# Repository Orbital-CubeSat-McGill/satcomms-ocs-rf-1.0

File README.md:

# satcomms-ocs-rf-1.0
OCS-RF-1.0 Project by OCS 3 (the green board)

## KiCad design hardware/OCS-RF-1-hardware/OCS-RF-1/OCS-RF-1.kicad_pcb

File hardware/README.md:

KiCad Project for the green board

library path should be added to enviorment variables to show up, or you can just import it with symbol/footprint editor

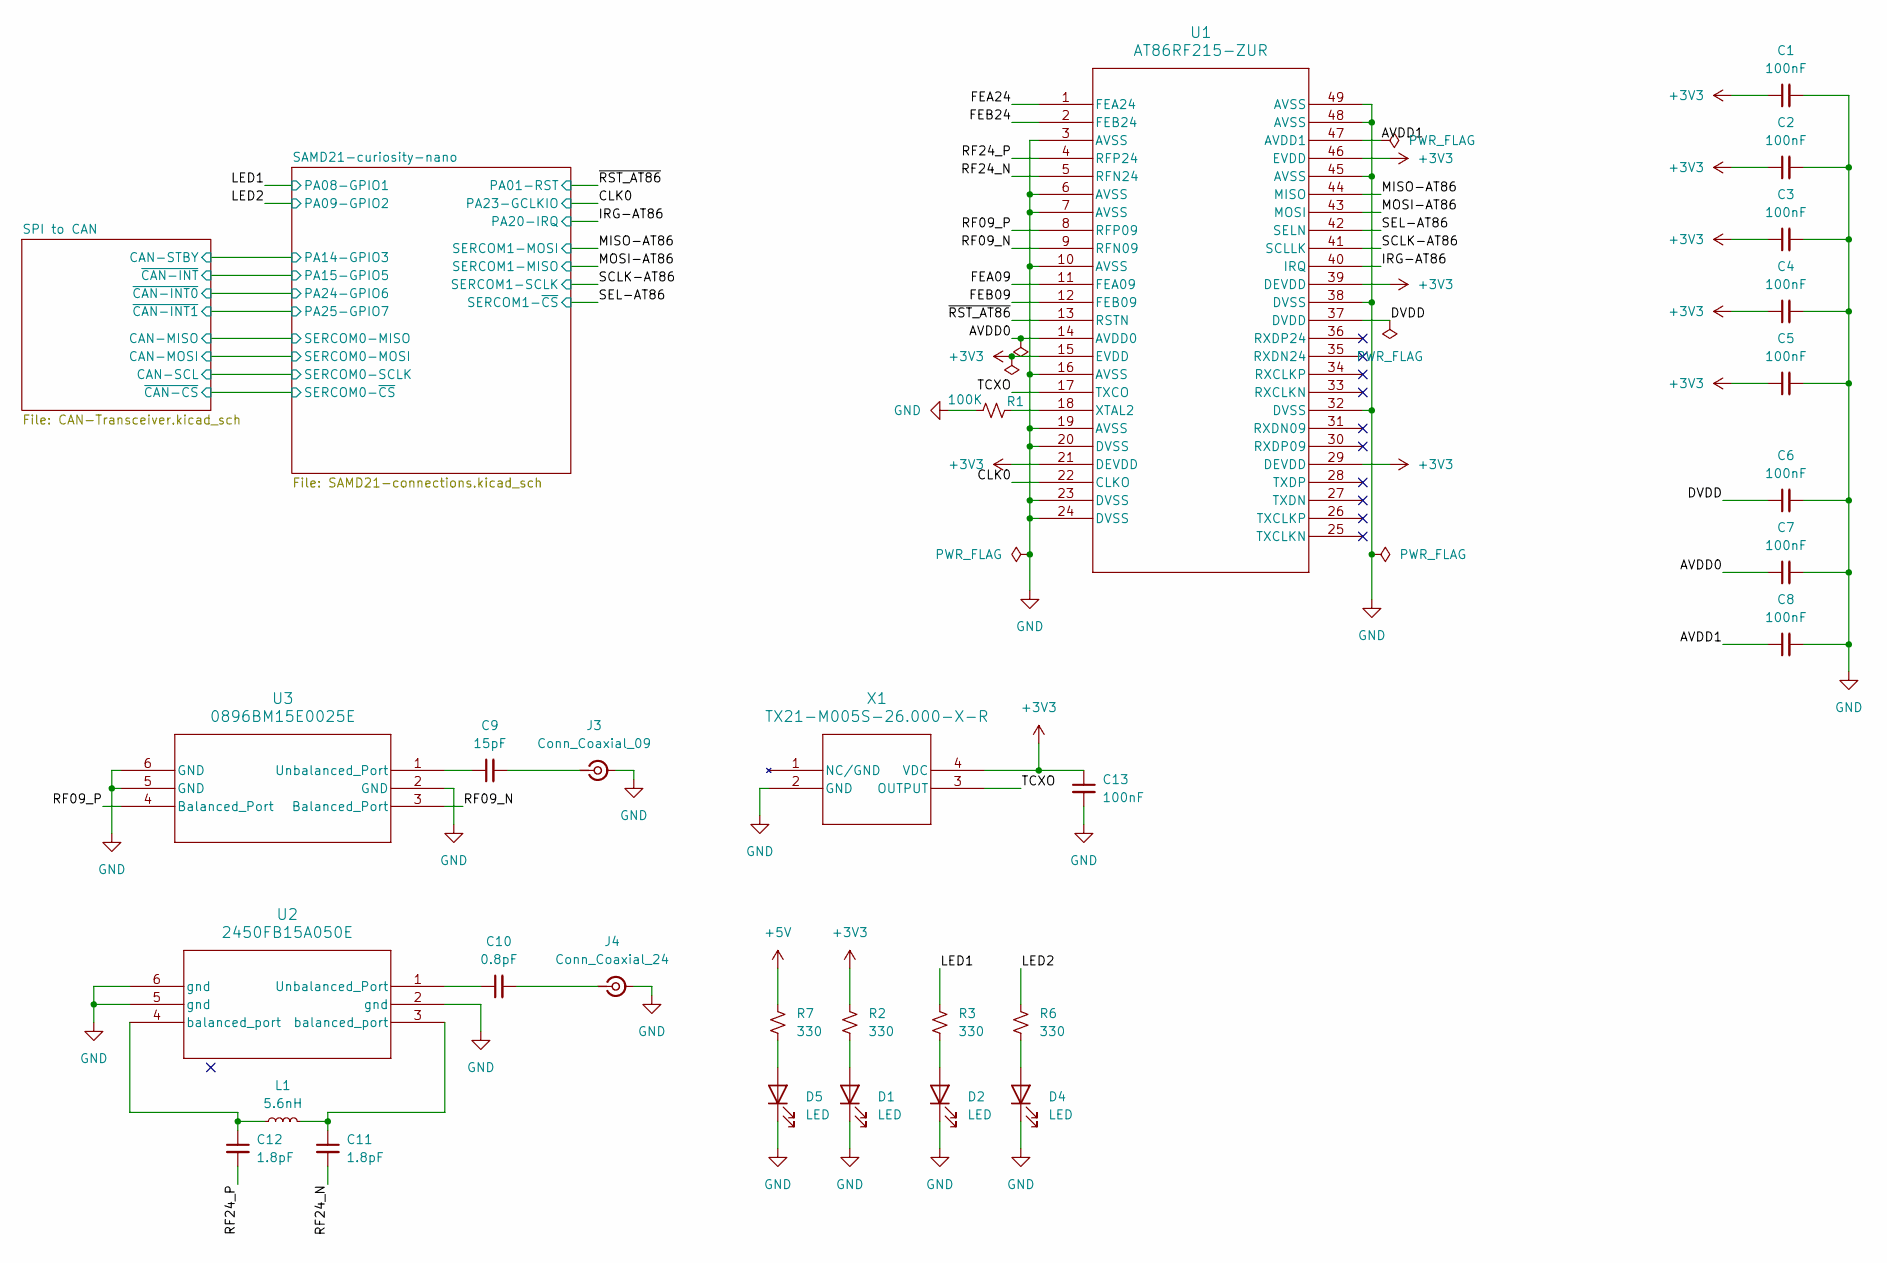
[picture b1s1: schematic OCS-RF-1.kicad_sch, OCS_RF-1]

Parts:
C1, C2, C3, C4, C5, C6, C7, C8, C13: 100nF; C_0603_1608Metric_Pad1.08x0.95mm_HandSolder
C9: 15pF; C_0402_1005Metric
C10: 0.8pF; C_0402_1005Metric
C11, C12: 1.8pF; C_0402_1005Metric
D1, D2, D4, D5: LED; LED_0603_1608Metric_Pad1.05x0.95mm_HandSolder
J3: Conn_Coaxial_09; SMA_Samtec_SMA-J-P-H-ST-EM1_EdgeMount
J4: Conn_Coaxial_24; SMA_Samtec_SMA-J-P-H-ST-EM1_EdgeMount
L1: 5.6nH; L_0402_1005Metric
R1: 100K; R_0603_1608Metric_Pad0.98x0.95mm_HandSolder
R2, R3, R6, R7: 330; R_0603_1608Metric_Pad0.98x0.95mm_HandSolder
U1: AT86RF215-ZUR; QFN48_PQ_MCH
U2: 2450FB15A050E; 2450FB15A050E_JOT
U3: 0896BM15E0025E; 0896BM15E0025E_JOT
X1: TX21-M005S-26.000-X-R; TX21_2x1p6_SMD_AKR

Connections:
+3V3: C1.1, C2.1, C3.1, C4.1, C5.1, C13.1, R2.1, U1.15 (EVDD), U1.21 (DEVDD), U1.29 (DEVDD), U1.39 (DEVDD), U1.46 (EVDD), X1.4 (VDC); also elsewhere on the board
+5V: R7.1; also elsewhere on the board
/AVDD0: C7.1, U1.14 (AVDD0)
/AVDD1: C8.1, U1.47 (AVDD1)
/CLK0: U1.22 (CLKO); also elsewhere on the board
/DVDD: C6.1, U1.37 (DVDD)
/FEA09: U1.11 (FEA09)
/FEA24: U1.1 (FEA24)
/FEB09: U1.12 (FEB09)
/FEB24: U1.2 (FEB24)
/IRG-AT86: U1.40 (IRQ); also elsewhere on the board
/LED1: R3.1; also elsewhere on the board
/LED2: R6.1; also elsewhere on the board
/MISO-AT86: U1.44 (MISO); also elsewhere on the board
/MOSI-AT86: U1.43 (MOSI); also elsewhere on the board
/RF09_N: U1.9 (RFN09), U3.3 (Balanced_Port)
/RF09_P: U1.8 (RFP09), U3.4 (Balanced_Port)
/RF24_N: C11.2, U1.5 (RFN24)
/RF24_P: C12.2, U1.4 (RFP24)
/SCLK-AT86: U1.41 (SCLLK); also elsewhere on the board
/SEL-AT86: U1.42 (SELN); also elsewhere on the board
/TCXO: U1.17 (TXCO), X1.3 (OUTPUT)
/~RST_AT86: U1.13 (RSTN); also elsewhere on the board
GND: C1.2, C2.2, C3.2, C4.2, C5.2, C6.2, C7.2, C8.2, C13.2, D1.1 (K), D2.1 (K), D4.1 (K), D5.1 (K), J3.2 (Ext), J4.2 (Ext), R1.2, U1.3 (AVSS), U1.6 (AVSS), U1.7 (AVSS), U1.10 (AVSS), U1.16 (AVSS), U1.19 (AVSS), U1.20 (DVSS), U1.23 (DVSS), U1.24 (DVSS), U1.32 (DVSS), U1.38 (DVSS), U1.45 (AVSS), U1.48 (AVSS), U1.49 (AVSS), U2.2 (gnd), U2.5 (gnd), U2.6 (gnd), U3.2 (GND), U3.5 (GND), U3.6 (GND), X1.2 (GND); also elsewhere on the board
unnamed: C11.1, L1.2, U2.3 (balanced_port)
unnamed: C12.1, L1.1, U2.4 (balanced_port)
unnamed: D1.2 (A), R2.2
unnamed: D2.2 (A), R3.2
unnamed: D4.2 (A), R6.2
unnamed: D5.2 (A), R7.2
unnamed: C9.2, J3.1 (In)
unnamed: C10.2, J4.1 (In)
unnamed: R1.1, U1.18 (XTAL2)
unnamed: C10.1, U2.1 (Unbalanced_Port)
unnamed: C9.1, U3.1 (Unbalanced_Port)

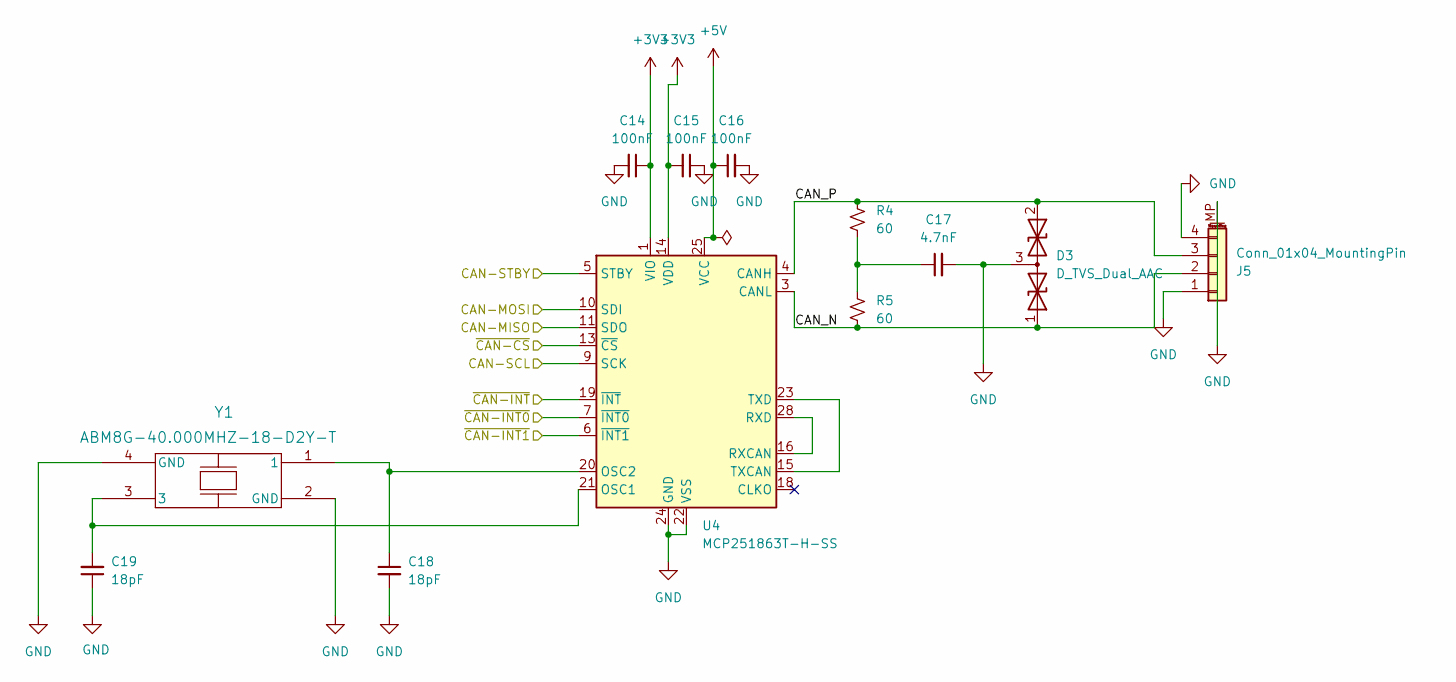
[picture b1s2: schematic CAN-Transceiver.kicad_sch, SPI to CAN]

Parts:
C14, C15, C16: 100nF; C_0603_1608Metric_Pad1.08x0.95mm_HandSolder
C17: 4.7nF; C_0603_1608Metric_Pad1.08x0.95mm_HandSolder
C18, C19: 18pF; C_0603_1608Metric_Pad1.08x0.95mm_HandSolder
D3: D_TVS_Dual_AAC; SOT-23
J5: Conn_01x04_MountingPin; JST_SH_SM04B-SRSS-TB_1x04-1MP_P1.00mm_Horizontal
R4, R5: 60; R_0603_1608Metric_Pad0.98x0.95mm_HandSolder
U4: MCP251863T-H-SS; SSOP-28_5.3x10.2mm_P0.65mm
Y1: ABM8G-40.000MHZ-18-D2Y-T; CRYSTAL_ABM8G_ABR

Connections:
+3V3: C14.1, C15.2, U4.1 (VIO), U4.14 (VDD); also elsewhere on the board
+5V: C16.1, U4.25 (VCC); also elsewhere on the board
/SAMD21-curiosity-nano/PA14-GPIO3: U4.5 (STBY); also elsewhere on the board
/SAMD21-curiosity-nano/PA15-GPIO5: U4.19 (~INT); also elsewhere on the board
/SAMD21-curiosity-nano/PA24-GPIO6: U4.7 (~INT0); also elsewhere on the board
/SAMD21-curiosity-nano/PA25-GPIO7: U4.6 (~INT1); also elsewhere on the board
/SAMD21-curiosity-nano/SERCOM0-MISO: U4.11 (SDO); also elsewhere on the board
/SAMD21-curiosity-nano/SERCOM0-MOSI: U4.10 (SDI); also elsewhere on the board
/SAMD21-curiosity-nano/SERCOM0-SCLK: U4.9 (SCK); also elsewhere on the board
/SAMD21-curiosity-nano/SERCOM0-~CS: U4.13 (~CS); also elsewhere on the board
/SPI to CAN/CAN_N: D3.1 (A1), J5.2, R5.2, U4.3 (CANL)
/SPI to CAN/CAN_P: D3.2 (A2), J5.3, R4.1, U4.4 (CANH)
GND: C14.2, C15.1, C16.2, C17.2, C18.2, C19.1, D3.3 (common), J5.1, J5.4, J5.MP (MountPin), U4.22 (VSS), U4.24 (GND), Y1.2 (GND), Y1.4 (GND); also elsewhere on the board
unnamed: C17.1, R4.2, R5.1
unnamed: C19.2, U4.21 (OSC1), Y1.3
unnamed: C18.1, U4.20 (OSC2), Y1.1
unnamed: U4.16 (RXCAN), U4.28 (RXD)
unnamed: U4.15 (TXCAN), U4.23 (TXD)

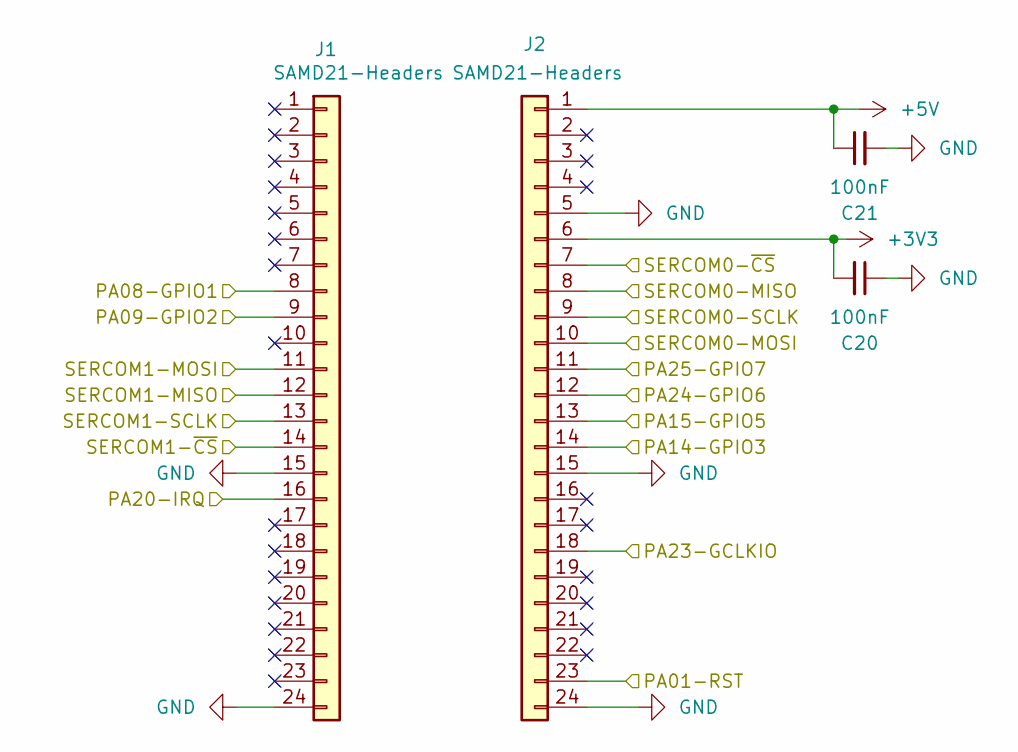
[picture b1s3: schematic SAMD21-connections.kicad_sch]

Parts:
C20, C21: 100nF; C_0603_1608Metric_Pad1.08x0.95mm_HandSolder
J1, J2: SAMD21-Headers; PinHeader_1x24_P2.54mm_Vertical

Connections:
+3V3: C20.2, J2.6; also elsewhere on the board
+5V: C21.1, J2.1; also elsewhere on the board
/CLK0: J2.18; also elsewhere on the board
/IRG-AT86: J1.16; also elsewhere on the board
/LED1: J1.8; also elsewhere on the board
/LED2: J1.9; also elsewhere on the board
/MISO-AT86: J1.11; also elsewhere on the board
/MOSI-AT86: J1.12; also elsewhere on the board
/SAMD21-curiosity-nano/PA14-GPIO3: J2.14; also elsewhere on the board
/SAMD21-curiosity-nano/PA15-GPIO5: J2.13; also elsewhere on the board
/SAMD21-curiosity-nano/PA24-GPIO6: J2.12; also elsewhere on the board
/SAMD21-curiosity-nano/PA25-GPIO7: J2.11; also elsewhere on the board
/SAMD21-curiosity-nano/SERCOM0-MISO: J2.8; also elsewhere on the board
/SAMD21-curiosity-nano/SERCOM0-MOSI: J2.10; also elsewhere on the board
/SAMD21-curiosity-nano/SERCOM0-SCLK: J2.9; also elsewhere on the board
/SAMD21-curiosity-nano/SERCOM0-~CS: J2.7; also elsewhere on the board
/SCLK-AT86: J1.13; also elsewhere on the board
/SEL-AT86: J1.14; also elsewhere on the board
/~RST_AT86: J2.23; also elsewhere on the board
GND: C20.1, C21.2, J1.15, J1.24, J2.5, J2.15, J2.24; also elsewhere on the board

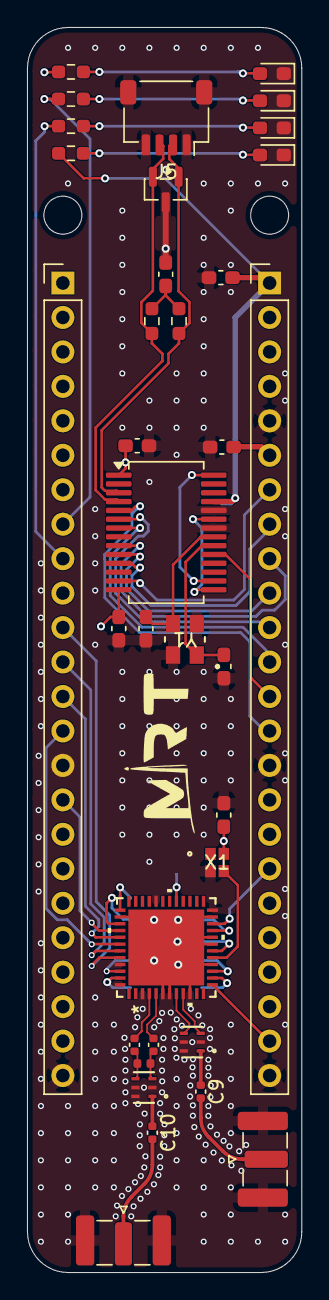
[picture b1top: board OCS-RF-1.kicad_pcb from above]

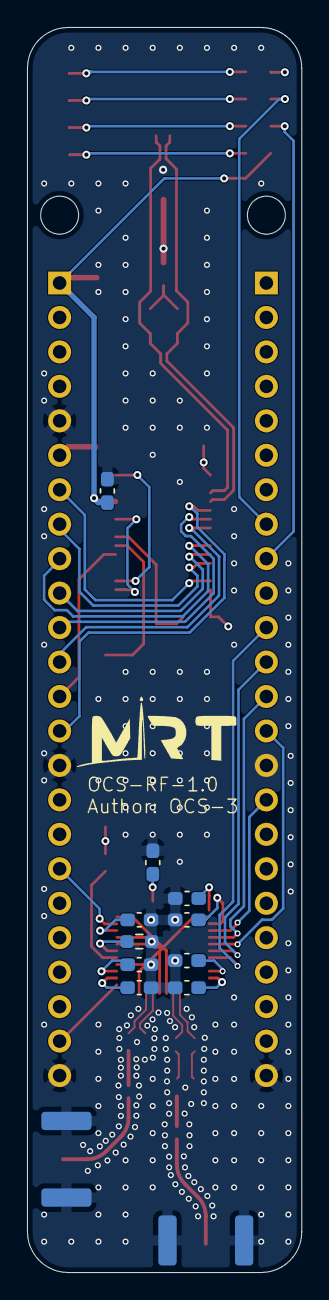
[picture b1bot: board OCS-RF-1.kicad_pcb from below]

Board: 4 copper layers, 20.2 x 91.8 mm, 45 parts (10 on the bottom side), 46 nets.
